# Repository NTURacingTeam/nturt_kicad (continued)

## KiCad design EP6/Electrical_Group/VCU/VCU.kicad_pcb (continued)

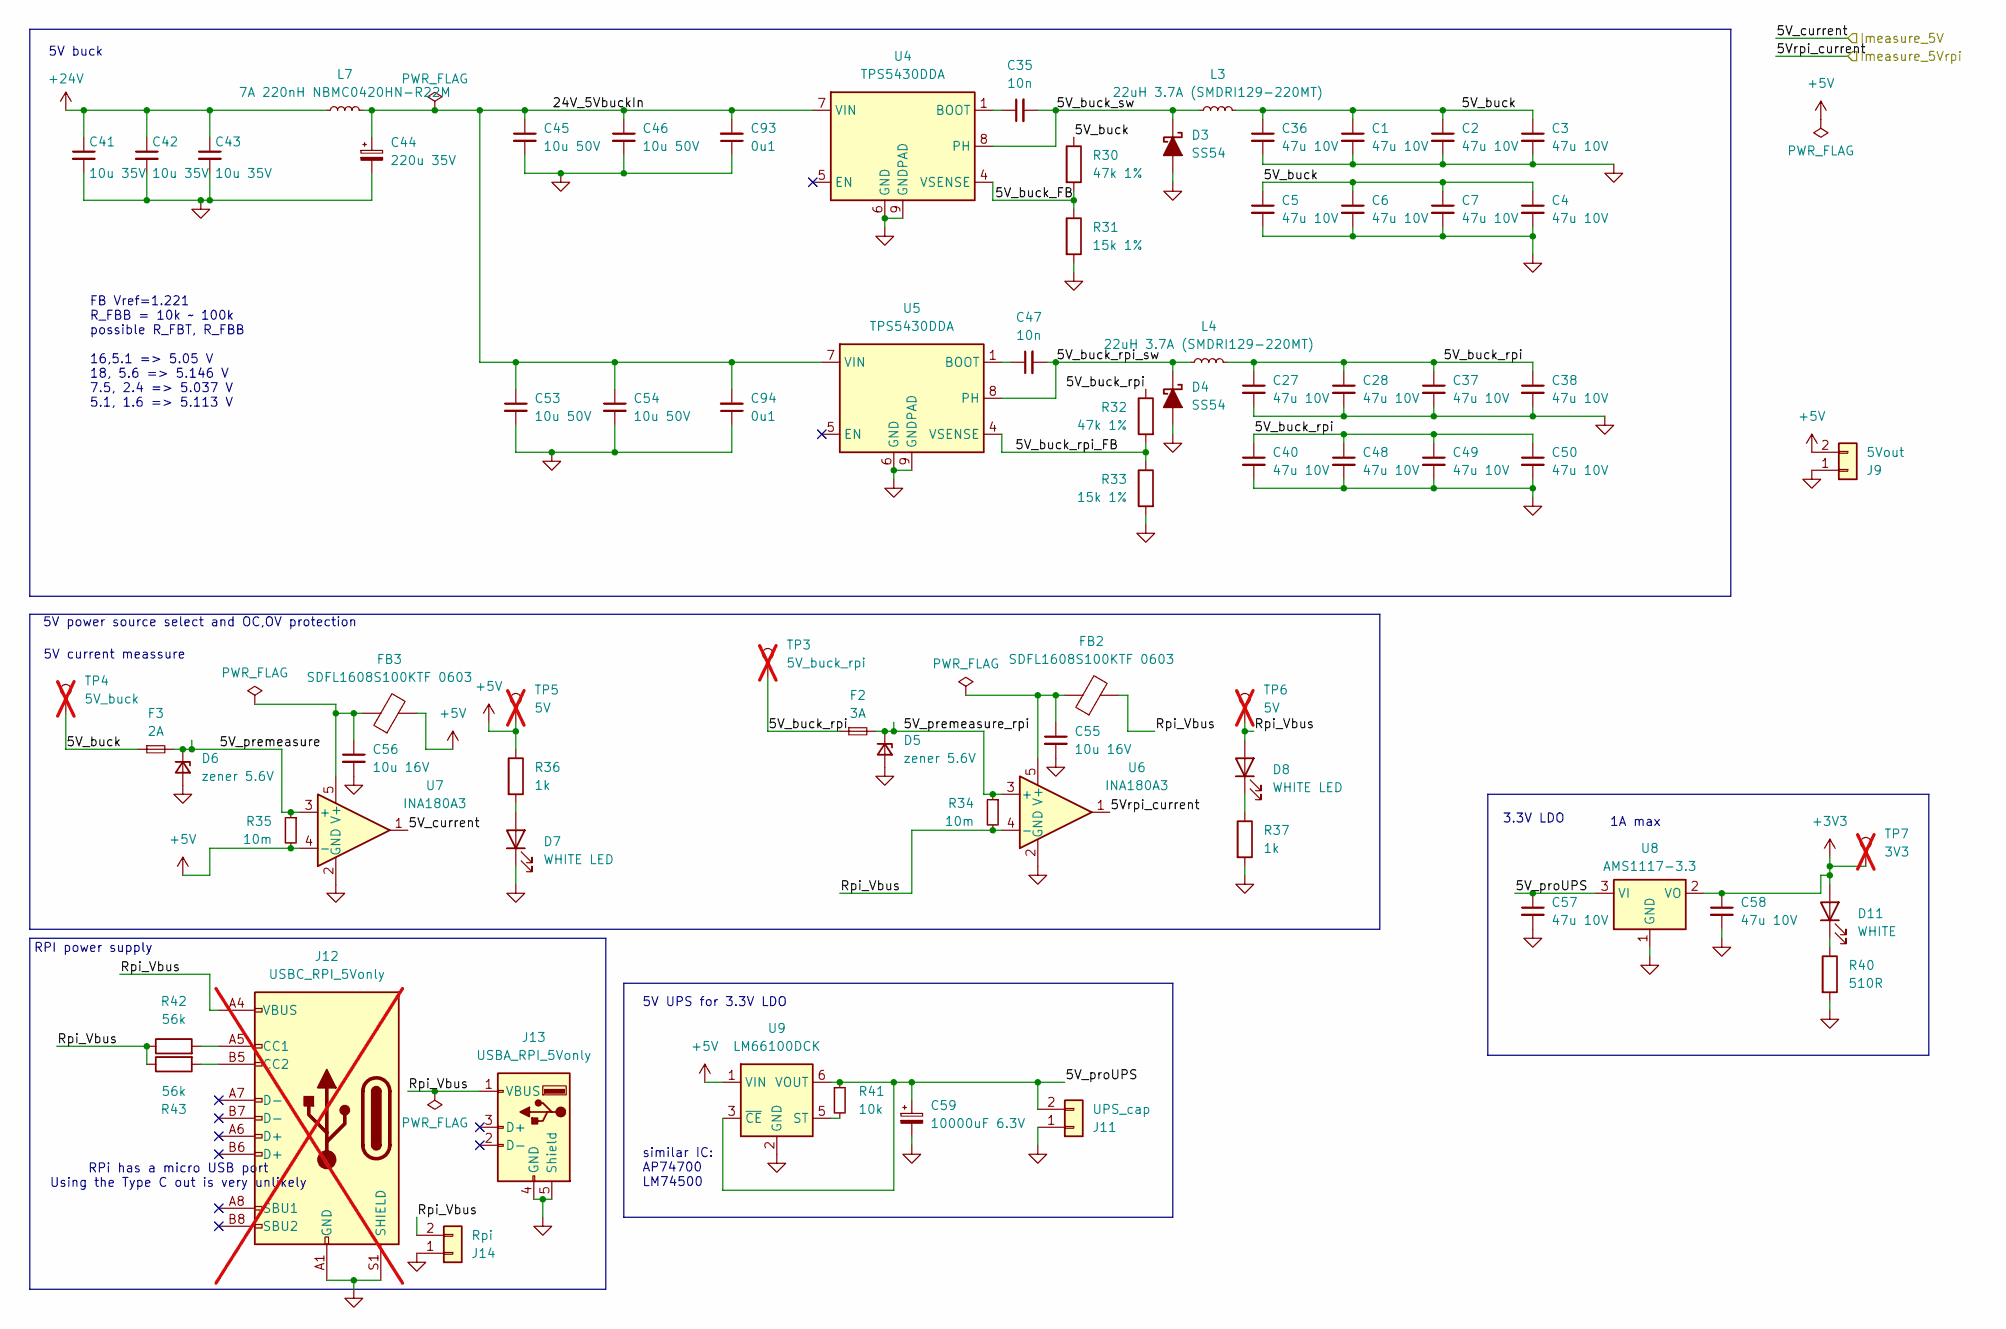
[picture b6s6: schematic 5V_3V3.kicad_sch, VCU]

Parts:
C1, C2, C3, C4, C5, C6, C7, C27, C28, C36, C37, C38, C40, C48, C49, C50, C57, C58: 47u 10V; C_1206_3216Metric
C35, C47: 10n; C_0603_1608Metric
C41, C42, C43: 10u 35V; C_1206_3216Metric
C44: 220u 35V; CP_Radial_D8.0mm_P3.80mm
C45, C46, C53, C54: 10u 50V; C_1206_3216Metric
C55, C56: 10u 16V; C_0603_1608Metric
C59: 10000uF 6.3V; CP_Radial_D10.0mm_P5.00mm
C93, C94: 0u1; C_0603_1608Metric
D3, D4: SS54; D_SMA
D5: zener 5.6V; D_SMB
D6: zener 5.6V; D_SOD-123
D7, D8: WHITE LED; LED_0603_1608Metric
D11: WHITE; LED_0603_1608Metric
F2: 3A; Fuse_1206_3216Metric
F3: 2A; Fuse_1206_3216Metric
FB2, FB3: SDFL1608S100KTF 0603; L_0603_1608Metric
J9: 5Vout; JST_XH_B2B-XH-A_1x02_P2.50mm_Vertical
J11: UPS_cap; JST_PH_B2B-PH-K_1x02_P2.00mm_Vertical
J12: USBC_RPI_5Vonly; USB_C_Receptacle_GCT_USB4105-xx-A_16P_TopMnt_Horizontal; not fitted
J13: USBA_RPI_5Vonly; USB_A_Molex_67643_Horizontal
J14: Rpi; JST_XH_B2B-XH-A_1x02_P2.50mm_Vertical
L3, L4: 22uH 3.7A (SMDRI129-220MT); L_Bourns_SRR1260
L7: 7A 220nH NBMC0420HN-R22M; L_Ferrocore_DLG-0403
R30, R32: 47k 1%; R_0603_1608Metric
R31, R33: 15k 1%; R_0603_1608Metric
R34, R35: 10m; R_1206_3216Metric
R36, R37: 1k; R_0402_1005Metric
R40: 510R; R_0402_1005Metric
R41: 10k; R_0402_1005Metric
R42, R43: 56k; R_0402_1005Metric
TP3: 5V_buck_rpi; TestPoint_Pad_D1.0mm; not fitted
TP4: 5V_buck; TestPoint_Pad_D1.0mm; not fitted
TP5, TP6: 5V; TestPoint_Pad_D1.0mm; not fitted
TP7: 3V3; TestPoint_Pad_D1.0mm; not fitted
U4, U5: TPS5430DDA; TI_SO-PowerPAD-8_ThermalVias
U6, U7: INA180A3; SOT-23-5
U8: AMS1117-3.3; SOT-223-3_TabPin2
U9: LM66100DCK; SOT-363_SC-70-6

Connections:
+3V3: C58.1, D11.2 (A), TP7.1, U8.2 (VO); also elsewhere on the board
+5V: FB3.2, J9.2, R35.2, R36.1, TP5.1, U7.4 (-), U9.1 (VIN); also elsewhere on the board
+24V: C41.1, C42.1, C43.1, L7.1; also elsewhere on the board
/5V_3V3/5V_buck: C1.1, C2.1, C3.1, C4.1, C5.1, C6.1, C7.1, C36.1, F3.1, L3.2, R30.1, TP4.1
/5V_3V3/5V_buck_FB: R30.2, R31.1, U4.4 (VSENSE)
/5V_3V3/5V_buck_rpi: C27.1, C28.1, C37.1, C38.1, C40.1, C48.1, C49.1, C50.1, F2.1, L4.2, R32.1, TP3.1
/5V_3V3/5V_buck_rpi_FB: R32.2, R33.1, U5.4 (VSENSE)
/5V_3V3/5V_buck_rpi_sw: C47.2, D4.1 (K), L4.1, U5.8 (PH)
/5V_3V3/5V_buck_sw: C35.2, D3.1 (K), L3.1, U4.8 (PH)
/5V_3V3/5V_premeasure: D6.1 (K), F3.2, R35.1, U7.3 (+)
/5V_3V3/5V_premeasure_rpi: D5.1 (K), F2.2, R34.1, U6.3 (+)
/5V_3V3/5V_proUPS: C57.1, C59.1, J11.2, R41.1, U8.3 (VI), U9.3 (~CE), U9.6 (VOUT)
/5V_3V3/24V_5VbuckIn: C44.1, C45.1, C46.1, C53.1, C54.1, C93.2, C94.2, L7.2, U4.7 (VIN), U5.7 (VIN)
/5V_3V3/Rpi_Vbus: D8.2 (A), FB2.2, J12.A4 (VBUS), J12.A9 (VBUS), J12.B4 (VBUS), J12.B9 (VBUS), J13.1 (VBUS), J14.2, R34.2, R42.1, R43.1, TP6.1, U6.4 (-)
/I_measure_5v: U7.1; also elsewhere on the board
/I_measure_5vrpi: U6.1; also elsewhere on the board
GND: C1.2, C2.2, C3.2, C4.2, C5.2, C6.2, C7.2, C27.2, C28.2, C36.2, C37.2, C38.2, C40.2, C41.2, C42.2, C43.2, C44.2, C45.2, C46.2, C48.2, C49.2, C50.2, C53.2, C54.2, C55.2, C56.2, C57.2, C58.2, C59.2, C93.1, C94.1, D3.2 (A), D4.2 (A), D5.2 (A), D6.2 (A), D7.1 (K), J9.1, J11.1, J12.A1 (GND), J12.A12 (GND), J12.B1 (GND), J12.B12 (GND), J12.S1 (SHIELD), J13.4 (GND), J13.5 (Shield), J14.1, R31.2, R33.2, R37.2, R40.2, U4.6 (GND), U4.9 (GNDPAD), U5.6 (GND), U5.9 (GNDPAD), U6.2 (GND), U7.2 (GND), U8.1 (GND), U9.2 (GND); also elsewhere on the board
unnamed: D7.2 (A), R36.2
unnamed: D8.1 (K), R37.1
unnamed: D11.1 (K), R40.1
unnamed: J12.A5 (CC1), R42.2
unnamed: J12.B5 (CC2), R43.2
unnamed: C35.1, U4.1 (BOOT)
unnamed: C47.1, U5.1 (BOOT)
unnamed: C55.1, FB2.1, U6.5 (V+)
unnamed: C56.1, FB3.1, U7.5 (V+)
unnamed: R41.2, U9.5 (ST)

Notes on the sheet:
5V UPS for 3.3V LDO
5V power source select and OC,OV protection
RPI power supply
RPi has a micro USB port Using the Type C out is very unlikely
3.3V LDO
5V buck
5V current meassure
FB Vref=1.221 R_FBB = 10k ~ 100k possible R_FBT, R_FBB 16,5.1 => 5.05 V 18, 5.6 => 5.146 V 7.5, 2.4 => 5.037 V 5.1, 1.6 => 5.113 V
1A max
similar IC: AP74700 LM74500

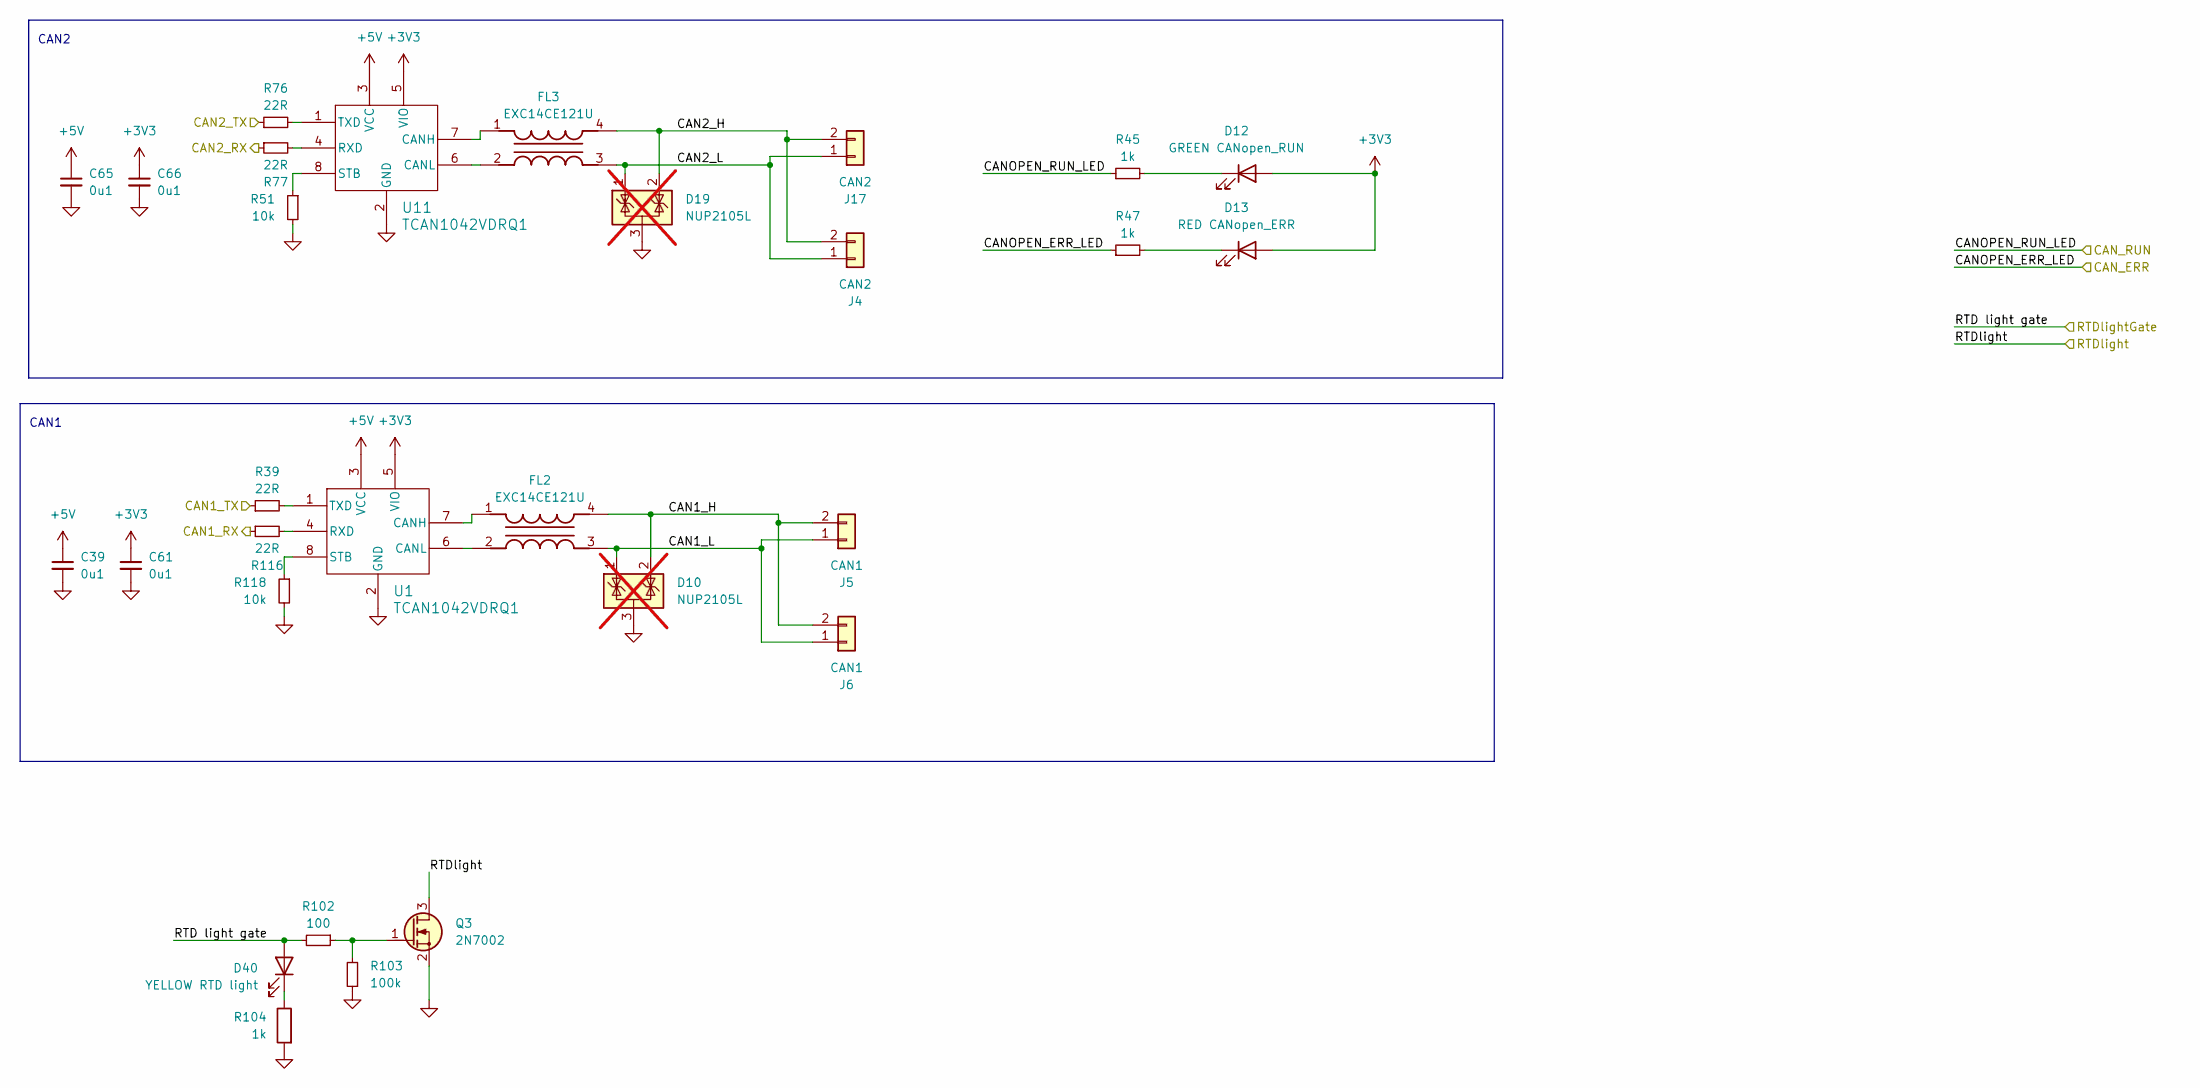
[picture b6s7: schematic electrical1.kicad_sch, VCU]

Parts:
C39, C61, C65, C66: 0u1; C_0402_1005Metric
D10, D19: NUP2105L; SOT-23; not fitted
D12: GREEN CANopen_RUN; LED_0603_1608Metric
D13: RED CANopen_ERR; LED_0603_1608Metric
D40: YELLOW RTD light; LED_0603_1608Metric
FL2, FL3: EXC14CE121U; EXCX4CE900U; Mouser Part Number 667-EXC-X4CE900U
J4, J17: CAN2; JST_XH_B2B-XH-A_1x02_P2.50mm_Vertical
J5, J6: CAN1; JST_XH_B2B-XH-A_1x02_P2.50mm_Vertical
Q3: 2N7002; SOT-23
R39, R76, R77, R116: 22R; R_0402_1005Metric
R45, R47, R104: 1k; R_0402_1005Metric
R51, R118: 10k; R_0402_1005Metric
R102: 100; R_0402_1005Metric
R103: 100k; R_0402_1005Metric
U1, U11: TCAN1042VDRQ1; SOIC-8_3.9x4.9mm_P1.27mm

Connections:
+3V3: C61.1, C66.1, D12.2 (A), D13.2 (A), U1.5 (VIO), U11.5 (VIO); also elsewhere on the board
+5V: C39.1, C65.1, U1.3 (VCC), U11.3 (VCC); also elsewhere on the board
/FDCAN1_RX: R116.1; also elsewhere on the board
/FDCAN1_TX: R39.1; also elsewhere on the board
/FDCAN2_RX: R76.1; also elsewhere on the board
/FDCAN2_TX: R77.1; also elsewhere on the board
/LED_CAN_ERR: R47.1; also elsewhere on the board
/LED_CAN_RUN: R45.1; also elsewhere on the board
/RTD light gate: D40.2 (A), R102.2; also elsewhere on the board
/RTDlight: Q3.3 (D); also elsewhere on the board
/electrical1/CAN1_H: D10.2 (K), FL2.4, J5.2, J6.2
/electrical1/CAN1_L: D10.1 (K), FL2.3, J5.1, J6.1
/electrical1/CAN2_H: D19.2 (K), FL3.4, J4.2, J17.2
/electrical1/CAN2_L: D19.1 (K), FL3.3, J4.1, J17.1
GND: C39.2, C61.2, C65.2, C66.2, D10.3 (A), D19.3 (A), Q3.2 (S), R51.2, R103.1, R104.2, R118.2, U1.2 (GND), U11.2 (GND); also elsewhere on the board
unnamed: D12.1 (K), R45.2
unnamed: D13.1 (K), R47.2
unnamed: D40.1 (K), R104.1
unnamed: Q3.1 (G), R102.1, R103.2
unnamed: FL2.1, U1.7 (CANH)
unnamed: FL2.2, U1.6 (CANL)
unnamed: R116.2, U1.4 (RXD)
unnamed: R118.1, U1.8 (STB)
unnamed: R39.2, U1.1 (TXD)
unnamed: FL3.1, U11.7 (CANH)
unnamed: FL3.2, U11.6 (CANL)
unnamed: R77.2, U11.4 (RXD)
unnamed: R51.1, U11.8 (STB)
unnamed: R76.2, U11.1 (TXD)

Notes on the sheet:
CAN1
CAN2

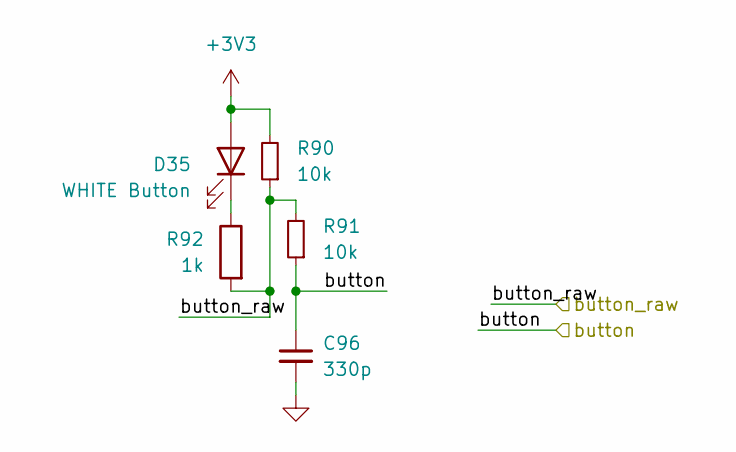
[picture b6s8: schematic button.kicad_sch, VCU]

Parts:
C96: 330p; C_0402_1005Metric
D35: WHITE Button; LED_0603_1608Metric
R90, R91: 10k; R_0402_1005Metric
R92: 1k; R_0402_1005Metric

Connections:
+3V3: D35.2 (A), R90.2; also elsewhere on the board
/button5: C96.1, R91.1; also elsewhere on the board
/button_raw5: R90.1, R91.2, R92.2; also elsewhere on the board
GND: C96.2; also elsewhere on the board
unnamed: D35.1 (K), R92.1

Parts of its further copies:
C68, C71, C72, C95, C97, C101: 330p; C_0402_1005Metric
D15, D20, D33, D34, D36, D37: WHITE Button; LED_0603_1608Metric
R55, R57, R81, R82, R84, R85, R87, R88, R93, R94, R107, R108: 10k; R_0402_1005Metric
R58, R83, R86, R89, R95, R109: 1k; R_0402_1005Metric

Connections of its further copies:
+3V3: D15.2 (A), D20.2 (A), D33.2 (A), D34.2 (A), D36.2 (A), D37.2 (A), R55.2, R81.2, R84.2, R87.2, R93.2, R107.2; also elsewhere on the board
/button1: C68.1, R57.1; also elsewhere on the board
/button2: C71.1, R82.1; also elsewhere on the board
/button3: C72.1, R85.1; also elsewhere on the board
/button4: C95.1, R88.1; also elsewhere on the board
/button6: C97.1, R94.1; also elsewhere on the board
/button7: C101.1, R108.1; also elsewhere on the board
/button_raw1: R55.1, R57.2, R58.2; also elsewhere on the board
/button_raw2: R81.1, R82.2, R83.2; also elsewhere on the board
/button_raw3: R84.1, R85.2, R86.2; also elsewhere on the board
/button_raw4: R87.1, R88.2, R89.2; also elsewhere on the board
/button_raw6: R93.1, R94.2, R95.2; also elsewhere on the board
/button_raw7: R107.1, R108.2, R109.2; also elsewhere on the board
GND: C68.2, C71.2, C72.2, C95.2, C97.2, C101.2; also elsewhere on the board
unnamed: D15.1 (K), R58.1
unnamed: D20.1 (K), R83.1
unnamed: D33.1 (K), R86.1
unnamed: D34.1 (K), R89.1
unnamed: D36.1 (K), R95.1
unnamed: D37.1 (K), R109.1

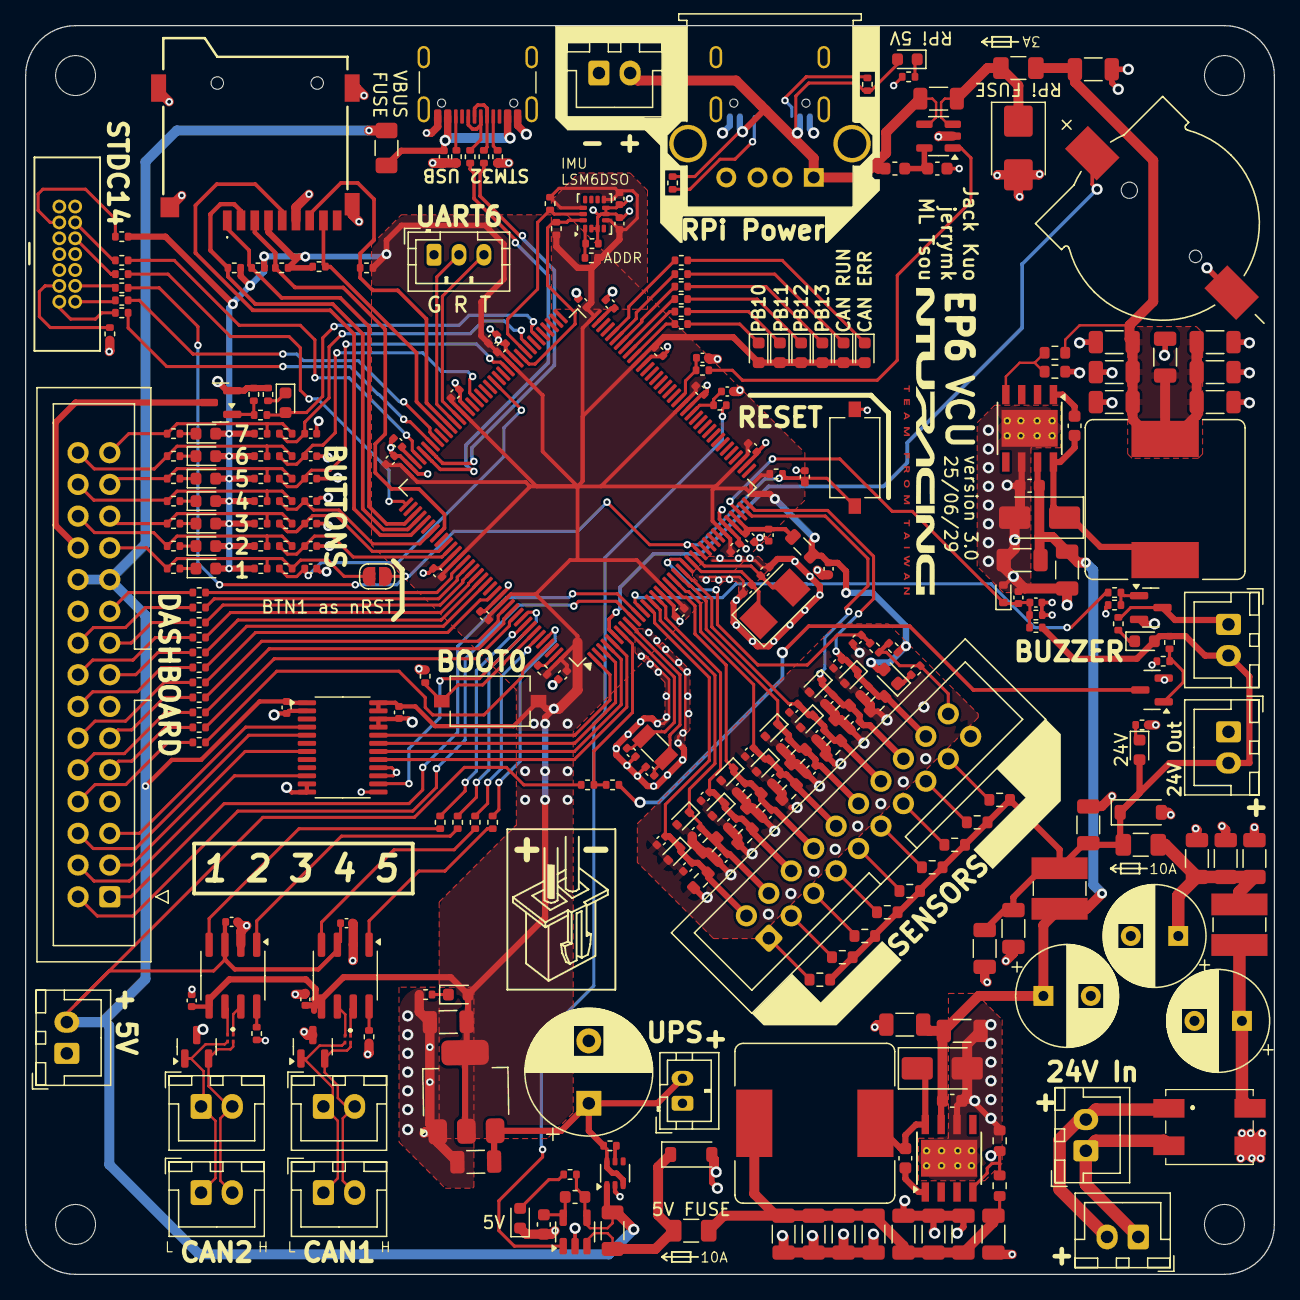
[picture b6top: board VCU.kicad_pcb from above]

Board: 4 copper layers, 100.0 x 100.0 mm, 309 parts (1 on the bottom side), 191 nets.

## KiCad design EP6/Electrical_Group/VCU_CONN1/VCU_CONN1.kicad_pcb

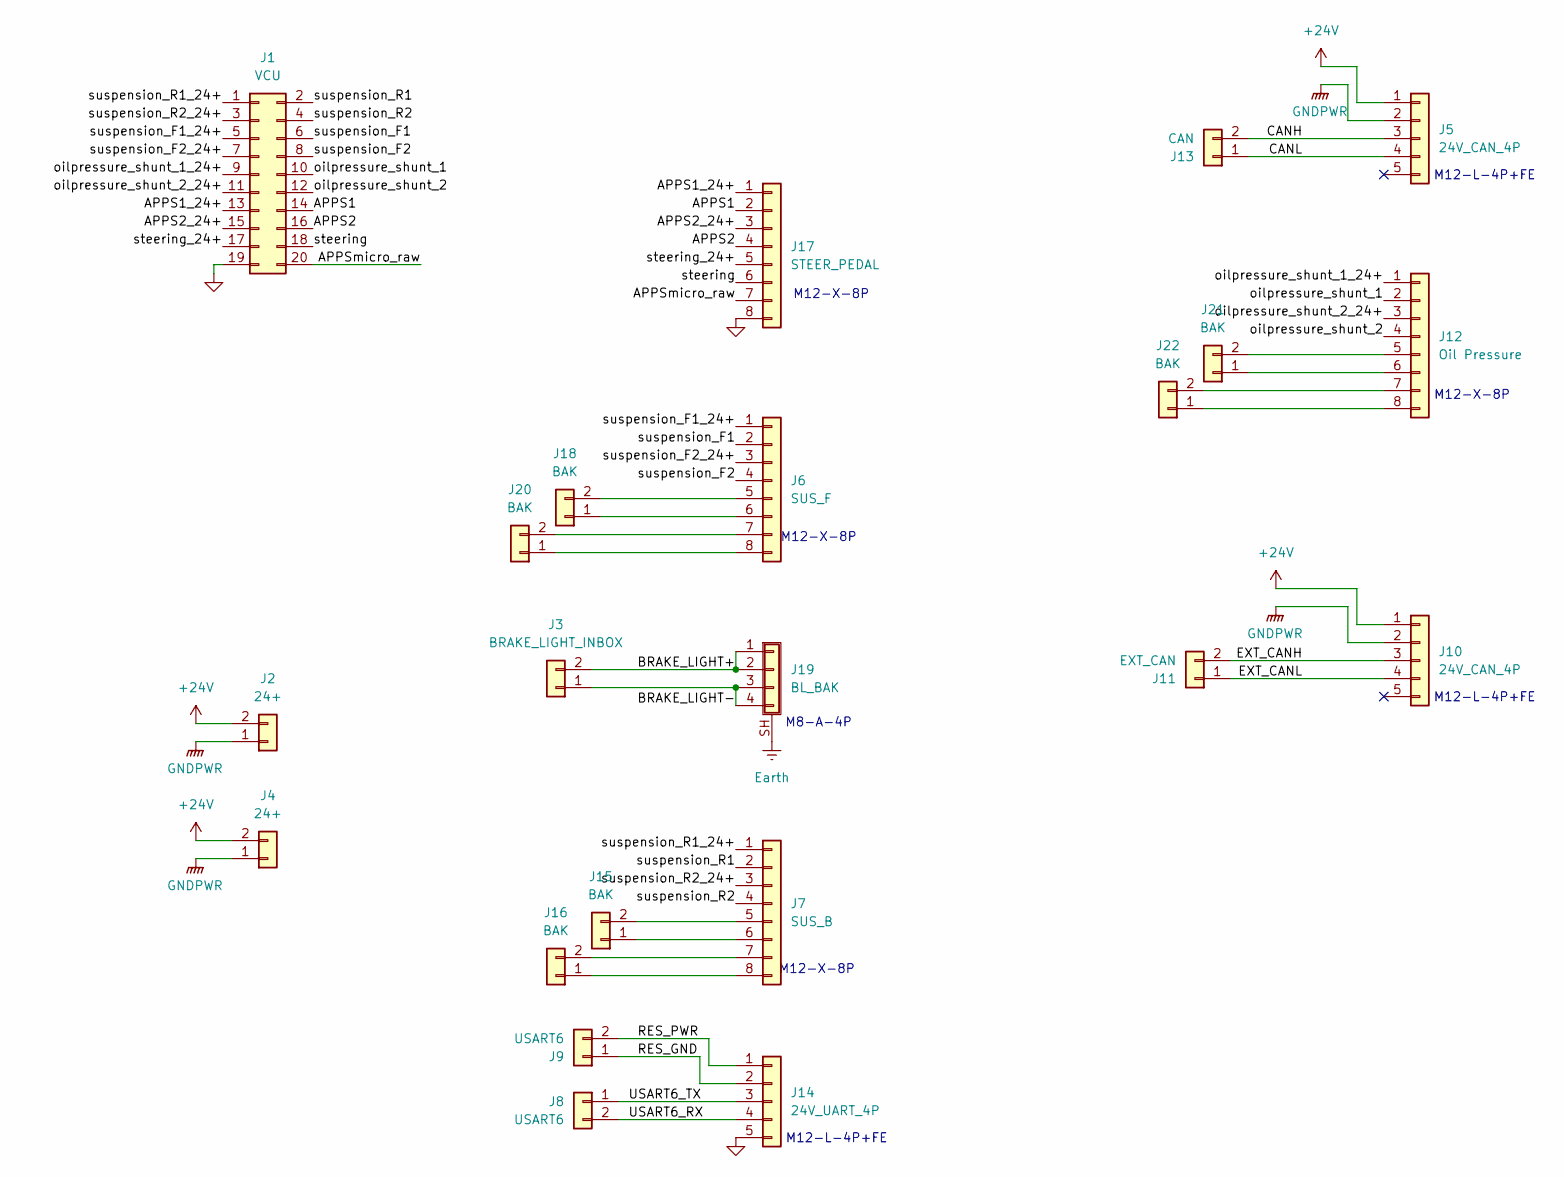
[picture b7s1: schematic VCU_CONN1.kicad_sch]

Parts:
J1: VCU; IDC-Header_2x10_P2.54mm_Vertical
J2, J4: 24+; JST_VH_B2P-VH_1x02_P3.96mm_Vertical
J3: BRAKE_LIGHT_INBOX; JST_XH_S2B-XH-A_1x02_P2.50mm_Horizontal
J5, J10: 24V_CAN_4P; NianYeong-M12-L-F5P
J6: SUS_F; NianYeong-M12-X-F4P
J7: SUS_B; NianYeong-M12-X-F4P
J8, J9: USART6; JST_XH_S2B-XH-A_1x02_P2.50mm_Horizontal
J11: EXT_CAN; JST_XH_S2B-XH-A_1x02_P2.50mm_Horizontal
J12: Oil Pressure; NianYeong-M12-X-F4P
J13: CAN; JST_XH_S2B-XH-A_1x02_P2.50mm_Horizontal
J14: 24V_UART_4P; NianYeong-M12-L-F5P
J15, J16, J18, J20, J21, J22: BAK; JST_XH_B2B-XH-A_1x02_P2.50mm_Vertical
J17: STEER_PEDAL; NianYeong-M12-X-F4P
J19: BL_BAK; WP-04F3-26-11

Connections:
+24V: J2.2, J4.2, J5.1, J10.1
/APPS1: J1.14, J17.2
/APPS1_24+: J1.13, J17.1
/APPS2: J1.16, J17.4
/APPS2_24+: J1.15, J17.3
/APPSmicro_raw: J1.20, J17.7
/BRAKE_LIGHT+: J3.2, J19.1, J19.2
/BRAKE_LIGHT-: J3.1, J19.3, J19.4
/CANH: J5.3, J13.2
/CANL: J5.4, J13.1
/EXT_CANH: J10.3, J11.2
/EXT_CANL: J10.4, J11.1
/RES_GND: J9.1, J14.2
/RES_PWR: J9.2, J14.1
/USART6_RX: J8.2, J14.4
/USART6_TX: J8.1, J14.3
/oilpressure_shunt_1: J1.10, J12.2
/oilpressure_shunt_1_24+: J1.9, J12.1
/oilpressure_shunt_2: J1.12, J12.4
/oilpressure_shunt_2_24+: J1.11, J12.3
/steering: J1.18, J17.6
/steering_24+: J1.17, J17.5
/suspension_F1: J1.6, J6.2
/suspension_F1_24+: J1.5, J6.1
/suspension_F2: J1.8, J6.4
/suspension_F2_24+: J1.7, J6.3
/suspension_R1: J1.2, J7.2
/suspension_R1_24+: J1.1, J7.1
/suspension_R2: J1.4, J7.4
/suspension_R2_24+: J1.3, J7.3
Earth: J19.SH (Shield)
GND: J1.19, J14.5, J17.8
GNDPWR: J2.1, J4.1, J5.2, J10.2
unnamed: J12.5, J21.2
unnamed: J12.6, J21.1
unnamed: J12.7, J22.2
unnamed: J12.8, J22.1
unnamed: J7.6, J15.1
unnamed: J7.5, J15.2
unnamed: J7.8, J16.1
unnamed: J7.7, J16.2
unnamed: J6.6, J18.1
unnamed: J6.5, J18.2
unnamed: J6.8, J20.1
unnamed: J6.7, J20.2

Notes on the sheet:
M12-X-8P
M12-L-4P+FE
M8-A-4P

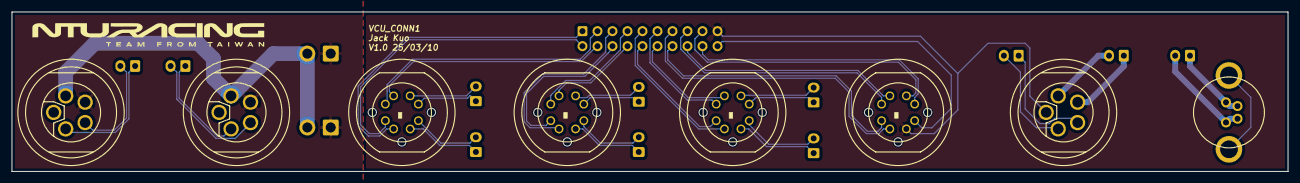
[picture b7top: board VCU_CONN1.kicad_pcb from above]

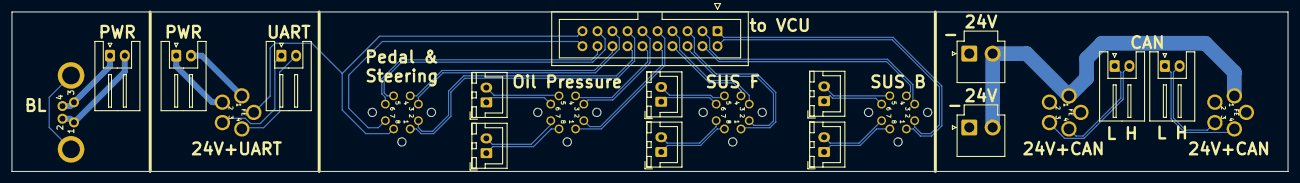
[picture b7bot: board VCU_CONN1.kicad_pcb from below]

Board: 2 copper layers, 216.0 x 27.0 mm, 22 parts (14 on the bottom side), 44 nets.
